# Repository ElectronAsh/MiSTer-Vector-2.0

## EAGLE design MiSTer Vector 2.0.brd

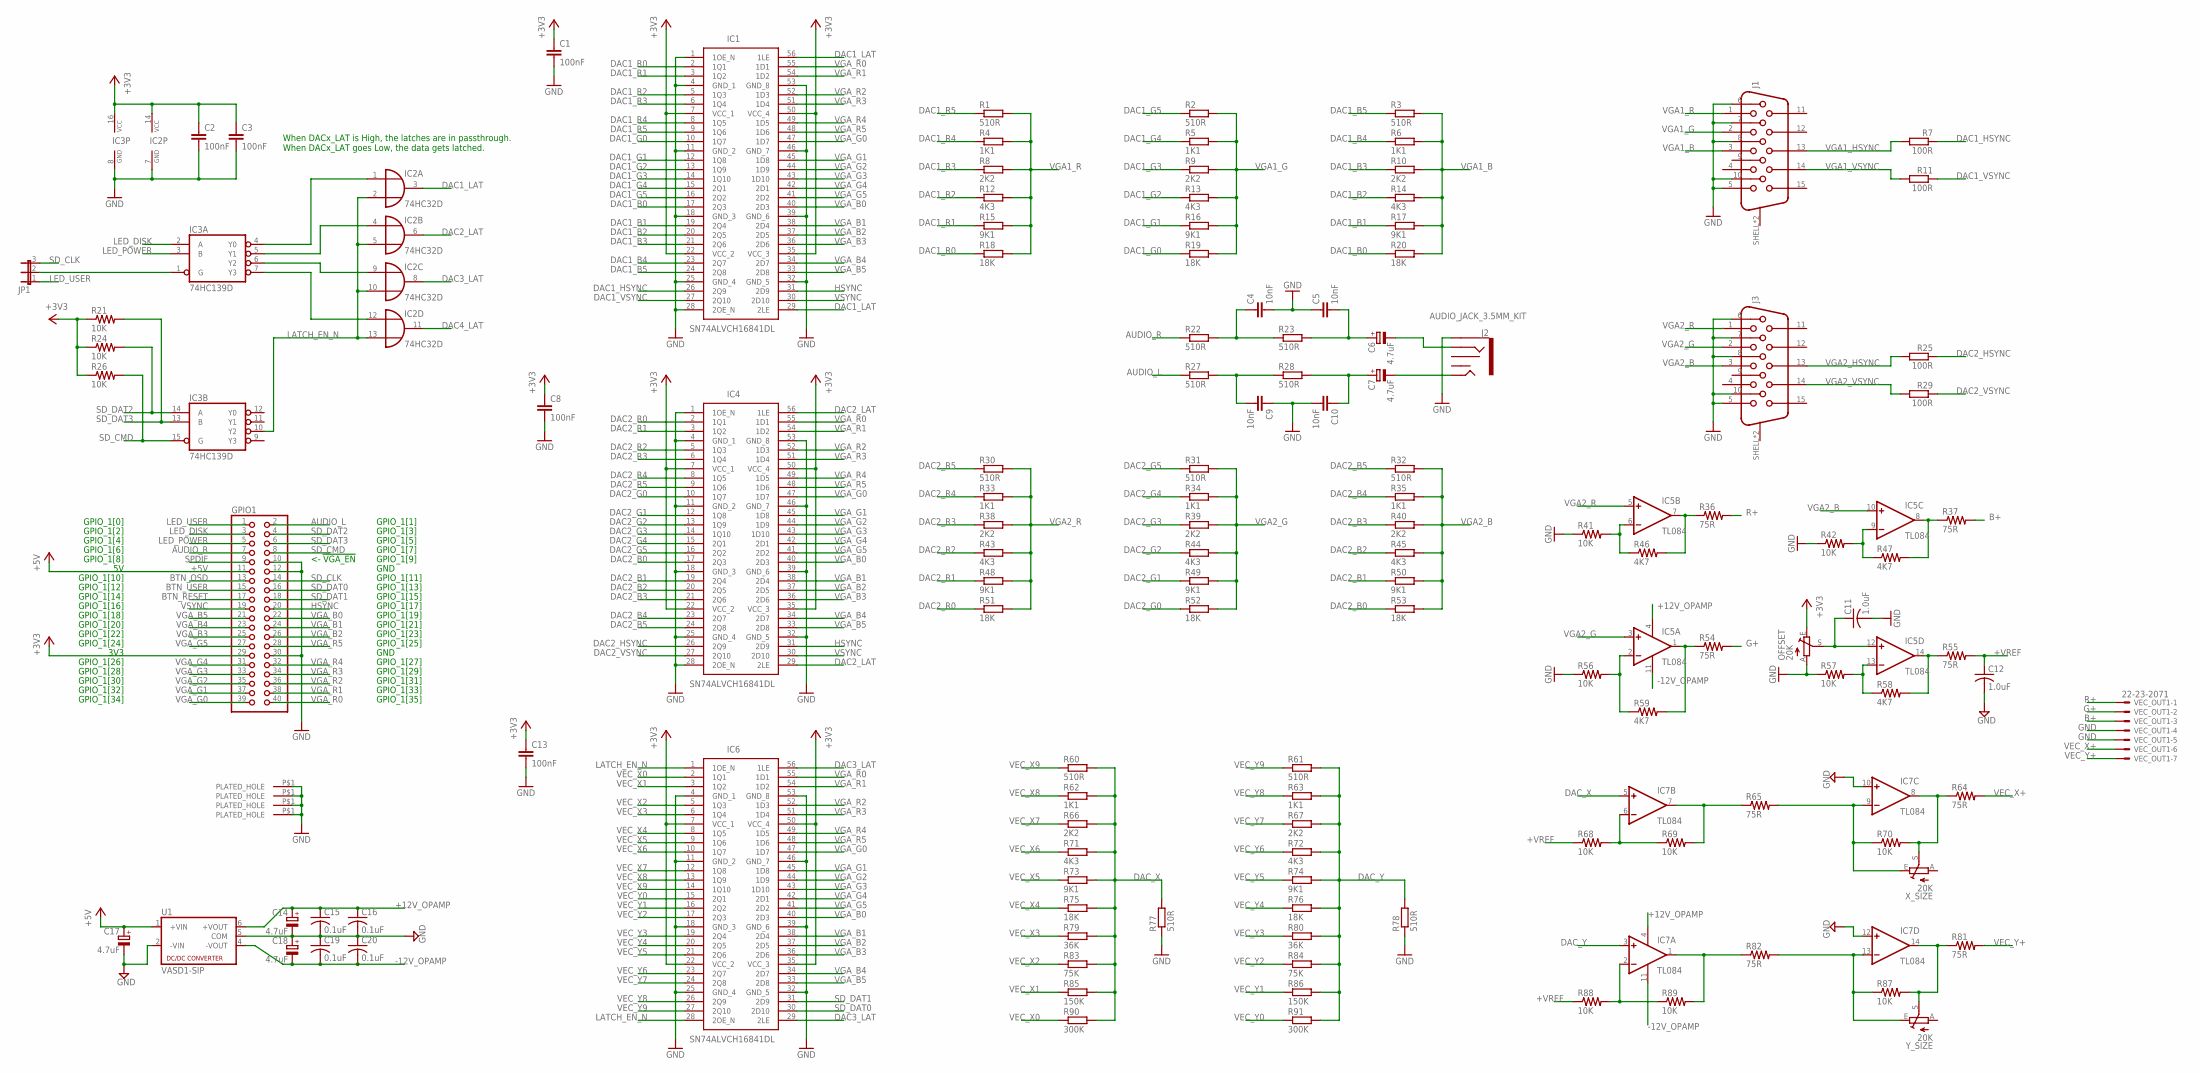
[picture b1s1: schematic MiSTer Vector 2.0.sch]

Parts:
C1, C2, C3, C8, C13: 100nF; C0603
C4, C5, C9, C10: 10nF; C0603
C6, C7, C14, C17, C18: 4.7uF; CT3528
C11, C12: 1.0uF; C0603
C15, C16, C19, C20: 0.1uF; C0603
GPIO1: PINHD-2X20; 2X20
IC1, IC4, IC6: SN74ALVCH16841DL; SOP50P810X120-56N
IC2: 74HC32D; SO14
IC3: 74HC139D; SO16
IC5, IC7: TL084; SOIC-14
J1, J3: 618015330923
J2: AUDIO_JACK_3.5MM_KIT; AUDIO-JACK-KIT
JP1: JP2E; JP2
OFFSET: 20K; B25P
R1, R2, R3, R22, R23, R27, R28, R30, R31, R32, R60, R61, R77, R78: 510R; R0603
R4, R5, R6, R33, R34, R35, R62, R63: 1K1; R0603
R7, R11, R25, R29: 100R; R0603
R8, R9, R10, R38, R39, R40, R66, R67: 2K2; R0603
R12, R13, R14, R43, R44, R45, R71, R72: 4K3; R0603
R15, R16, R17, R48, R49, R50, R73, R74: 9K1; R0603
R18, R19, R20, R51, R52, R53, R75, R76: 18K; R0603
R21, R24, R26, R41, R42, R56, R57, R68, R69, R70, R87, R88, R89: 10K; R0603
R36, R37, R54, R55, R64, R65, R81, R82: 75R; R0603
R46, R47, R58, R59: 4K7; R0603
R79, R80: 36K; R0603
R83, R84: 75K; R0603
R85, R86: 150K; R0603
R90, R91: 300K; R0603
U1: VASD1-SIP; NMA
U$1, U$2, U$3, U$4: PLATED_HOLE3.6MM; PLATED_HOLE_3.6MM
VEC_OUT1: 22-23-2071
X_SIZE: 20K; B25P
Y_SIZE: 20K; B25P

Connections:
+3V3: C1.1, C2.1, C3.1, C8.1, C13.1, GPIO1.29, IC1.7 (VCC_1), IC1.22 (VCC_2), IC1.35 (VCC_3), IC1.50 (VCC_4), IC2.14 (VCC), IC3.16 (VCC), IC4.7 (VCC_1), IC4.22 (VCC_2), IC4.35 (VCC_3), IC4.50 (VCC_4), IC6.7 (VCC_1), IC6.22 (VCC_2), IC6.35 (VCC_3), IC6.50 (VCC_4), OFFSET.E, R21.1, R24.1, R26.1
+5V: C17.+, GPIO1.11, U1.1 (+VIN)
+12V_OPAMP: C14.+, C15.1, C16.1, IC5.4 (V+), IC7.4 (V+), U1.6 (+VOUT)
+VREF: C12.1, R55.2, R68.1, R88.1
-12V_OPAMP: C18.-, C19.2, C20.2, IC5.11 (V-), IC7.11 (V-), U1.4 (-VOUT)
AUDIO_L: GPIO1.2, R27.1
AUDIO_R: GPIO1.7, R22.1
B1+: IC5.8 (OUT), R37.1, R47.2
B+: R37.2, VEC_OUT1.3
BTN_OSD: GPIO1.13
BTN_RESET: GPIO1.17
BTN_USER: GPIO1.15
DAC1_B0: IC1.17 (2Q3), R20.1
DAC1_B1: IC1.19 (2Q4), R17.1
DAC1_B2: IC1.20 (2Q5), R14.1
DAC1_B3: IC1.21 (2Q6), R10.1
DAC1_B4: IC1.23 (2Q7), R6.1
DAC1_B5: IC1.24 (2Q8), R3.1
DAC1_G0: IC1.10 (1Q7), R19.1
DAC1_G1: IC1.12 (1Q8), R16.1
DAC1_G2: IC1.13 (1Q9), R13.1
DAC1_G3: IC1.14 (1Q10), R9.1
DAC1_G4: IC1.15 (2Q1), R5.1
DAC1_G5: IC1.16 (2Q2), R2.1
DAC1_HSYNC: IC1.26 (2Q9), R7.1
DAC1_LAT: IC1.29 (2LE), IC1.56 (1LE), IC2.3 (O)
DAC1_R0: IC1.2 (1Q1), R18.1
DAC1_R1: IC1.3 (1Q2), R15.1
DAC1_R2: IC1.5 (1Q3), R12.1
DAC1_R3: IC1.6 (1Q4), R8.1
DAC1_R4: IC1.8 (1Q5), R4.1
DAC1_R5: IC1.9 (1Q6), R1.1
DAC1_VSYNC: IC1.27 (2Q10), R11.1
DAC2_B0: IC4.17 (2Q3), R53.1
DAC2_B1: IC4.19 (2Q4), R50.1
DAC2_B2: IC4.20 (2Q5), R45.1
DAC2_B3: IC4.21 (2Q6), R40.1
DAC2_B4: IC4.23 (2Q7), R35.1
DAC2_B5: IC4.24 (2Q8), R32.1
DAC2_G0: IC4.10 (1Q7), R52.1
DAC2_G1: IC4.12 (1Q8), R49.1
DAC2_G2: IC4.13 (1Q9), R44.1
DAC2_G3: IC4.14 (1Q10), R39.1
DAC2_G4: IC4.15 (2Q1), R34.1
DAC2_G5: IC4.16 (2Q2), R31.1
DAC2_HSYNC: IC4.26 (2Q9), R25.1
DAC2_LAT: IC2.6 (O), IC4.29 (2LE), IC4.56 (1LE)
DAC2_R0: IC4.2 (1Q1), R51.1
DAC2_R1: IC4.3 (1Q2), R48.1
DAC2_R2: IC4.5 (1Q3), R43.1
DAC2_R3: IC4.6 (1Q4), R38.1
DAC2_R4: IC4.8 (1Q5), R33.1
DAC2_R5: IC4.9 (1Q6), R30.1
DAC2_VSYNC: IC4.27 (2Q10), R29.1
DAC3_LAT: IC2.8 (O), IC6.29 (2LE), IC6.56 (1LE)
DAC4_LAT: IC2.11 (O)
DAC_X: IC7.5 (+IN), R60.2, R62.2, R66.2, R71.2, R73.2, R75.2, R77.2, R79.2, R83.2, R85.2, R90.2
DAC_Y: IC7.3 (+IN), R61.2, R63.2, R67.2, R72.2, R74.2, R76.2, R78.2, R80.2, R84.2, R86.2, R91.2
G1+: IC5.1 (OUT), R54.1, R59.2
G+: R54.2, VEC_OUT1.2
GND: C1.2, C2.2, C3.2, C4.2, C5.1, C8.2, C9.1, C10.2, C11.2, C12.2, C13.2, C14.-, C15.2, C16.2, C17.-, C18.+, C19.1, C20.1, GPIO1.10, GPIO1.12, GPIO1.30, IC1.1 (1OE_N), IC1.4 (GND_1), IC1.11 (GND_2), IC1.18 (GND_3), IC1.25 (GND_4), IC1.28 (2OE_N), IC1.32 (GND_5), IC1.39 (GND_6), IC1.46 (GND_7), IC1.53 (GND_8), IC2.7 (GND), IC3.8 (GND), IC4.1 (1OE_N), IC4.4 (GND_1), IC4.11 (GND_2), IC4.18 (GND_3), IC4.25 (GND_4), IC4.28 (2OE_N), IC4.32 (GND_5), IC4.39 (GND_6), IC4.46 (GND_7), IC4.53 (GND_8), IC6.4 (GND_1), IC6.11 (GND_2), IC6.18 (GND_3), IC6.25 (GND_4), IC6.32 (GND_5), IC6.39 (GND_6), IC6.46 (GND_7), IC6.53 (GND_8), IC7.10 (+IN), IC7.12 (+IN), J1.5, J1.6, J1.7, J1.8, J1.10, J2.SLEEVE, J3.5, J3.6, J3.7, J3.8, J3.10, OFFSET.A, R41.1, R42.1, R56.1, R57.1, R77.1, R78.1, U1.2 (-VIN), U1.5 (COM), U$1.P$1, U$2.P$1, U$3.P$1, U$4.P$1, VEC_OUT1.4, VEC_OUT1.5
HSYNC: GPIO1.20, IC1.31 (2D9), IC4.31 (2D9)
I1+: IC5.14 (OUT), R55.1, R58.2
LATCH_EN_N: IC2.2 (I1), IC2.5 (I1), IC2.10 (I1), IC2.13 (I1), IC3.10 (Y2), IC6.1 (1OE_N), IC6.28 (2OE_N)
LED_DISK: GPIO1.3, IC3.2 (A)
LED_POWER: GPIO1.5, IC3.3 (B)
LED_USER: GPIO1.1, JP1.1
unnamed: C11.1, IC5.12 (+IN), OFFSET.S
unnamed: IC3.1 (G), JP1.2
unnamed: C6.-, J2.RING
unnamed: C9.2, R27.2, R28.1
unnamed: C7.+, C10.1, R28.2
unnamed: C7.-, J2.TIP
unnamed: C4.1, R22.2, R23.1
unnamed: C5.2, C6.+, R23.2
unnamed: IC2.1 (I0), IC3.4 (Y0)
unnamed: IC2.4 (I0), IC3.5 (Y1)
unnamed: IC2.9 (I0), IC3.6 (Y2)
unnamed: IC2.12 (I0), IC3.7 (Y3)
unnamed: IC7.6 (-IN), R68.2, R69.1
unnamed: IC7.2 (-IN), R88.2, R89.1
unnamed: IC7.7 (OUT), R65.1, R69.2
unnamed: IC7.9 (-IN), R65.2, R70.1, X_SIZE.E
unnamed: IC7.13 (-IN), R82.2, R87.1, Y_SIZE.E
unnamed: IC7.14 (OUT), R81.1, R87.2, Y_SIZE.S
unnamed: IC7.8 (OUT), R64.1, R70.2, X_SIZE.S
unnamed: IC7.1 (OUT), R82.1, R89.2
unnamed: IC5.2 (-IN), R56.2, R59.1
unnamed: IC5.6 (-IN), R41.2, R46.1
unnamed: IC5.13 (-IN), R57.2, R58.1
unnamed: IC5.9 (-IN), R42.2, R47.1
R1+: IC5.7 (OUT), R36.1, R46.2
R+: R36.2, VEC_OUT1.1
SD_CLK: GPIO1.14, JP1.3
SD_CMD: GPIO1.8, IC3.15 (G), R26.2
SD_DAT0: GPIO1.16, IC6.30 (2D10)
SD_DAT1: GPIO1.18, IC6.31 (2D9)
SD_DAT2: GPIO1.4, IC3.14 (A), R24.2
SD_DAT3: GPIO1.6, IC3.13 (B), R21.2
SPDIF: GPIO1.9
VEC_X0: IC6.2 (1Q1), R90.1
VEC_X1: IC6.3 (1Q2), R85.1
VEC_X2: IC6.5 (1Q3), R83.1
VEC_X3: IC6.6 (1Q4), R79.1
VEC_X4: IC6.8 (1Q5), R75.1
VEC_X5: IC6.9 (1Q6), R73.1
VEC_X6: IC6.10 (1Q7), R71.1
VEC_X7: IC6.12 (1Q8), R66.1
VEC_X8: IC6.13 (1Q9), R62.1
VEC_X9: IC6.14 (1Q10), R60.1
VEC_X+: R64.2, VEC_OUT1.6
VEC_Y0: IC6.15 (2Q1), R91.1
VEC_Y1: IC6.16 (2Q2), R86.1
VEC_Y2: IC6.17 (2Q3), R84.1
VEC_Y3: IC6.19 (2Q4), R80.1
VEC_Y4: IC6.20 (2Q5), R76.1
VEC_Y5: IC6.21 (2Q6), R74.1
VEC_Y6: IC6.23 (2Q7), R72.1
VEC_Y7: IC6.24 (2Q8), R67.1
VEC_Y8: IC6.26 (2Q9), R63.1
VEC_Y9: IC6.27 (2Q10), R61.1
VEC_Y+: R81.2, VEC_OUT1.7
VGA1_B: J1.3, R3.2, R6.2, R10.2, R14.2, R17.2, R20.2
VGA1_G: J1.2, R2.2, R5.2, R9.2, R13.2, R16.2, R19.2
VGA1_HSYNC: J1.13, R7.2
VGA1_R: J1.1, R1.2, R4.2, R8.2, R12.2, R15.2, R18.2
VGA1_VSYNC: J1.14, R11.2
VGA2_B: IC5.10 (+IN), J3.3, R32.2, R35.2, R40.2, R45.2, R50.2, R53.2
VGA2_G: IC5.3 (+IN), J3.2, R31.2, R34.2, R39.2, R44.2, R49.2, R52.2
VGA2_HSYNC: J3.13, R25.2
VGA2_R: IC5.5 (+IN), J3.1, R30.2, R33.2, R38.2, R43.2, R48.2, R51.2
VGA2_VSYNC: J3.14, R29.2
VGA_B0: GPIO1.22, IC1.40 (2D3), IC4.40 (2D3), IC6.40 (2D3)
VGA_B1: GPIO1.24, IC1.38 (2D4), IC4.38 (2D4), IC6.38 (2D4)
VGA_B2: GPIO1.26, IC1.37 (2D5), IC4.37 (2D5), IC6.37 (2D5)
VGA_B3: GPIO1.25, IC1.36 (2D6), IC4.36 (2D6), IC6.36 (2D6)
VGA_B4: GPIO1.23, IC1.34 (2D7), IC4.34 (2D7), IC6.34 (2D7)
VGA_B5: GPIO1.21, IC1.33 (2D8), IC4.33 (2D8), IC6.33 (2D8)
VGA_G0: GPIO1.39, IC1.47 (1D7), IC4.47 (1D7), IC6.47 (1D7)
VGA_G1: GPIO1.37, IC1.45 (1D8), IC4.45 (1D8), IC6.45 (1D8)
VGA_G2: GPIO1.35, IC1.44 (1D9), IC4.44 (1D9), IC6.44 (1D9)
VGA_G3: GPIO1.33, IC1.43 (1D10), IC4.43 (1D10), IC6.43 (1D10)
VGA_G4: GPIO1.31, IC1.42 (2D1), IC4.42 (2D1), IC6.42 (2D1)
VGA_G5: GPIO1.27, IC1.41 (2D2), IC4.41 (2D2), IC6.41 (2D2)
VGA_R0: GPIO1.40, IC1.55 (1D1), IC4.55 (1D1), IC6.55 (1D1)
VGA_R1: GPIO1.38, IC1.54 (1D2), IC4.54 (1D2), IC6.54 (1D2)
VGA_R2: GPIO1.36, IC1.52 (1D3), IC4.52 (1D3), IC6.52 (1D3)
VGA_R3: GPIO1.34, IC1.51 (1D4), IC4.51 (1D4), IC6.51 (1D4)
VGA_R4: GPIO1.32, IC1.49 (1D5), IC4.49 (1D5), IC6.49 (1D5)
VGA_R5: GPIO1.28, IC1.48 (1D6), IC4.48 (1D6), IC6.48 (1D6)
VSYNC: GPIO1.19, IC1.30 (2D10), IC4.30 (2D10)

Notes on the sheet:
GPIO_1[35]
GPIO_1[34]
GPIO_1[33]
GPIO_1[32]
GPIO_1[31]
GPIO_1[30]
GPIO_1[29]
GPIO_1[28]
GPIO_1[27]
GPIO_1[26]
GPIO_1[25]
GPIO_1[24]
GPIO_1[23]
GPIO_1[22]
GPIO_1[21]
GPIO_1[20]
GPIO_1[19]
GPIO_1[18]
GPIO_1[17]
GPIO_1[16]
GPIO_1[15]
GPIO_1[14]
GPIO_1[13]
GPIO_1[12]
GPIO_1[11]
GPIO_1[10]
GPIO_1[9]
GPIO_1[8]
GPIO_1[7]
GPIO_1[6]
GPIO_1[5]
GPIO_1[4]
GPIO_1[3]
GPIO_1[2]
GPIO_1[1]
GPIO_1[0]
GND
3V3
<- !VGA_EN
When DACx_LAT is High, the latches are in passthrough. When DACx_LAT goes Low, the data gets latched.

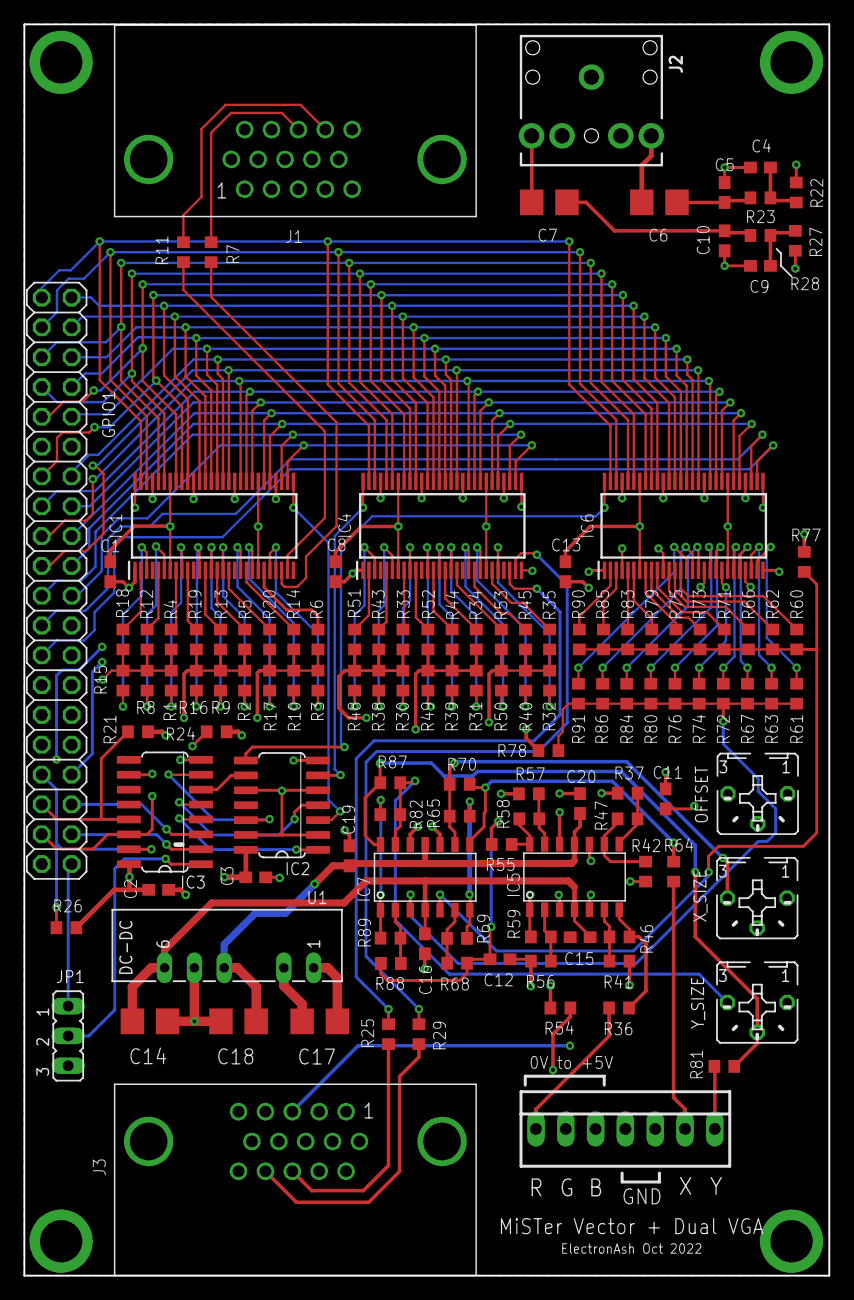
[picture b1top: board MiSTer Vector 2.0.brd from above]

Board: 4 copper layers, 68.6 x 106.6 mm, 132 parts (0 on the bottom side), 146 nets.

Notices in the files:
parts and their libraries:
con-wurth: Copyright: Würth Elektronik
SparkFun-Connectors: Licensing: Creative Commons ShareAlike 4.0 International - https://creativecommons.org/licenses/by-sa/4.0
